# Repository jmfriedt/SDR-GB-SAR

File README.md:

# SDR-GB-SAR

Opensource, openhardware implementation of a Software Defined Radio (SDR) Ground Based Synthetic-Aperture RADAR (GB-SAR [1])

The instrument is a Ground-Based Synthetic-Aperture-RADAR using a commercial, off the shelf WiFi dongle as pseudo-random
spectrum spread radiofrequency source, a Raspberry Pi 4 for data acquisition and antenna position control, and an Ettus
Research B210 SDR dual channel receiver for RADAR data acquisition.

The rail for moving the antenna set is a commercial, off the shelf device from <a href="https://www.iai-robot.co.jp/">IAI (Japan)</a>.

The radiofrequency signal source is an [Alfa Network AWUS036ACS](https://www.amazon.com/Network-AWUS036ACS-Wide-Coverage-Dual-Band-High-Sensitivity/dp/B0752CTSGD) WiFi USB dongle selected to cover the 5.8 GHz band and fitted with an RP-SMA antenna connector well adapted to be used, after converting [RP-SMA to SMA](https://www.digikey.fr/fr/products/detail/w%C3%BCrth-elektronik/64430203111000/10107023), to a [coupler](https://www.minicircuits.com/WebStore/dashboard.html?model=ZADC-10-63-S%2B) whose straight output feeds the horn antenna and coupled output feeds the reference channel of the [B210 SDR](https://www.ettus.com/all-products/ub210-kit/). The second input of the SDR is connected straight to the reception horn antenna.

[1] Hoonyol Lee and Jihyun Moon, Analysis of a Bistatic Ground-Based Synthetic Aperture Radar 
System and Indoor Experiments, MDPI Remote Sens. 2021, 13(1), 63; https://doi.org/10.3390/rs13010063 

## Connections

## Cost estimate

<table>
  <tr><td>Ainfo 4.9 to 7.05 GHz horn antenna (20 dB gain) LB-159-20-C-SF</td><td> 807 euros/p x2</td></tr>
  <tr><td>Ainfo mount bracket LB-159-10-C-MBL </td><td>202 euros/p x2</td></tr>
  <tr><td>IAI rail RCP5-BA6-WA-42P-48-2000-P3-S-CJT </td><td>1965+395 (software) euros</td></tr>
  <tr><td>B210 SDR </td><td>1854 euros (8 Feb. 2023)</td></tr>
  <tr><td>Raspberry Pi + misc. hardware (e.g. 3.3V to 24V converter) </td><td>200 euros</td></tr>
  <tr><td>MiniCircuits radiofrequency hardware (coupler ZADC-10-64, attenuators)</td><td> 72+~200</td></tr>
  <tr><td>WiFi dongle </td><td>~30 euros</td></tr>
  <tr><td>Total </td><td> 6734 euros</td></tr>
</table>

## Power consumption

<table>
  <tr><td>Motorized rail</td><td>500 mA/24V = 12 W</td></tr>
  <tr><td>Raspberry Pi 4</td><td> 300 mA/5V = 1.5 W</td></tr>
  <tr><td>B210 SDR</td><td> 210 mA/12V=2.5 W</td></tr>
  <tr><td>WiFi dongle (USB standard)</td><td> $<$500 mA/5V=2.5W</td></tr>
  <tr><td>Total</td><td> 18.5 W
</table>

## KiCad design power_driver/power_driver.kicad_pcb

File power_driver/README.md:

KiCAD files for the 0-3.3V to 24-0V driver for the Raspberry Pi 4 using the ULN2003 Darlington
transistor array. Notice the Darlington transistor acts as an inverter so that 0V command will
provide a 24V output and 3.3V GPIO command will lead to a 0V output.

TODO: double the ULN2003 for more outputs to allow for more than 64 steps (done manually by stacking
a second chip on top of the first, only sharing ping 8 and 9 for GND and 24V respectively).

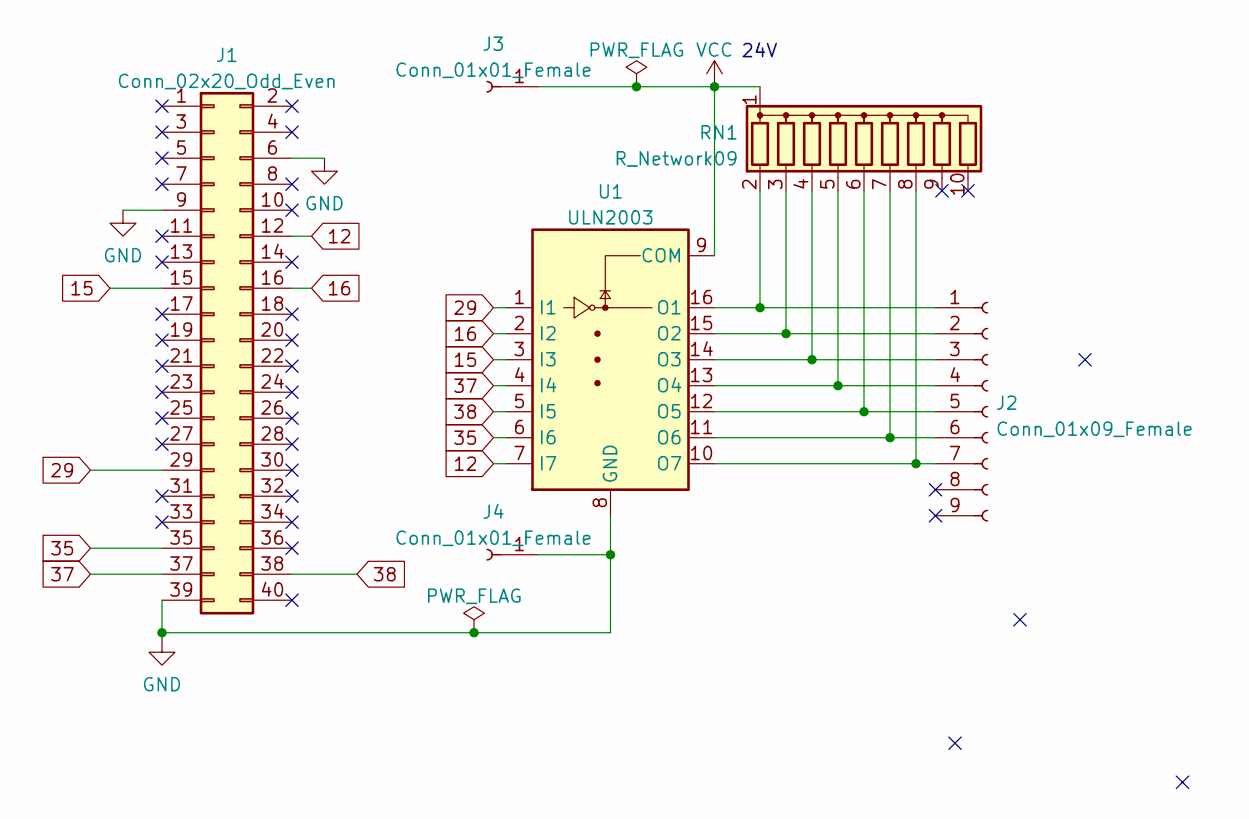
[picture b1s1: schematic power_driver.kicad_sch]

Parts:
J1: Conn_02x20_Odd_Even; PinSocket_2x20_P2.54mm_Vertical
J2: Conn_01x09_Female; PinSocket_1x09_P2.54mm_Vertical
J3, J4: Conn_01x01_Female; SolderWire-2sqmm_1x01_D2mm_OD3.9mm
RN1: R_Network09; R_Array_SIP10
U1: ULN2003; DIP-16_W7.62mm

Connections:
12: J1.12, U1.7 (I7)
15: J1.15, U1.3 (I3)
16: J1.16, U1.2 (I2)
29: J1.29, U1.1 (I1)
35: J1.35, U1.6 (I6)
37: J1.37, U1.4 (I4)
38: J1.38, U1.5 (I5)
GND: J1.6, J1.9, J1.39, J4.1, U1.8 (GND)
unnamed: J2.1, RN1.2 (R1), U1.16 (O1)
unnamed: J2.2, RN1.3 (R2), U1.15 (O2)
unnamed: J2.3, RN1.4 (R3), U1.14 (O3)
unnamed: J2.4, RN1.5 (R4), U1.13 (O4)
unnamed: J2.5, RN1.6 (R5), U1.12 (O5)
unnamed: J2.6, RN1.7 (R6), U1.11 (O6)
unnamed: J2.7, RN1.8 (R7), U1.10 (O7)
VCC: J3.1, RN1.1 (common), U1.9 (COM)

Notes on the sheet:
24V

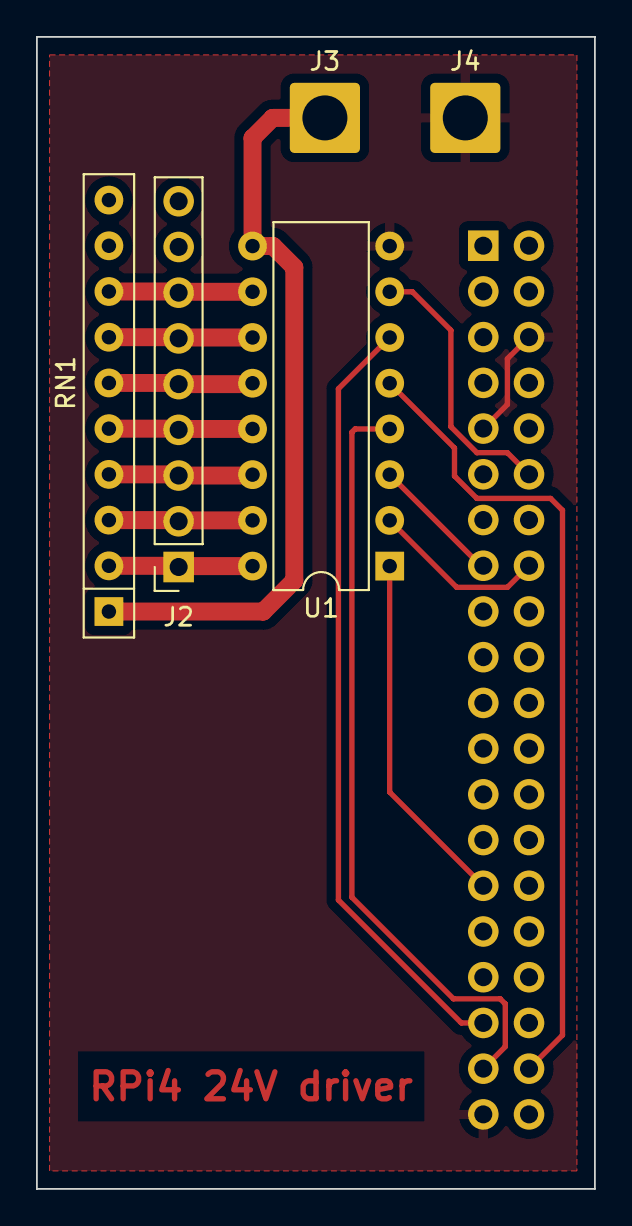
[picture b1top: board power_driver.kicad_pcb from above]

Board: 2 copper layers, 31.0 x 64.0 mm, 6 parts (1 on the bottom side), 16 nets.

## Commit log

2023-08-01 initial commit: CAD files
2023-08-01 CAD file
2023-08-17 azimuth range compression successful
2023-08-17 power_driver
2024-01-27 update scripts
2024-12-20 add power and cost estimate
2025-03-22 repeat measurement and write manual
2025-05-25 add DSI removal
